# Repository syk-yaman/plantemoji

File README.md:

# Plantemoji: a smart IoT plant caring system

A smart plant caring and irrigation device with a web infrastructure to monitor and control plants environment and explain their living state in emojis. Basically, your plant will have AI and will be able to talk with you using emojis!

Plant container			          							 |Water bucket	 
:-----------------------------------------------------------:|:-------------------------------------------------------------------------:|
|   

## Repository Content Summary

1. **3D Enclosures**

   This section includes the 3D printed parts, namely Fusion360 project files and STLs.

   - [Plant pot](</3D Enclosures/Plant pot/>)
   - [Water bucket](</3D Enclosures/Water bucket/>)

2. **Code**

   Includes micro-controllers' code, Artificial Intelligence code and various assets used during development.

   - [AI](/Code/AI)

     [LSTM.py](/Code/AI/LSTM.py) is the main Python script where the LSTM neural network is developed and trained. This folder also contains the old [Colab experiments](/Code/AI/Colab expirements/), which are obsolete and currently kept for archiving purposes. Finally, the [Results](/Code/AI/Results/) folder, which contains experiments' charts for both the LSTM.py and the obsolete Colab experiments.

   - [Assets](/Code/Assets)

     Contains `.bmp` files to be visualised on the screen, in addition to their original Photoshop files `.psd`

   - [ATMega8A](/Code/ATMega8A)

     C program for the AVR micro-controller.

   - [ESP32](/Code/ESP32)

     C++ code for the main micro-controller, which will replace Huzzah.

   - [Huzzah](/Code/Huzzah)

     C++ code for the old micro-controller. It will replaced by ESP32.

3. **Datasets**

   Includes 1 month dataset (the [full dataset](/Datasets/Full)) and other partial datasets used to train the AI model.

   This section also contains some [data analysis](/Datasets/Analysis/Analysis.md).

4. **Docs**

   This folder holds different kinds of documentation and images produced during project life time.

5. **PCB**

   The electronic side of the project. This section contains Eagle files and CAM outputs sent to PCB manufacturers.

6. **Server**

   Docker Composer file for InfluxDB and Grafana. Basically, all data acquisition is being managed by this Docker image.

## Project Overview

This conceptual diagram explains how the system is composed, down from reading sensors and understanding their values, and later sending them up to the cloud for further analysis and visualisation.

The objectives of this plant monitor are:
 - Interpret sensor data for the end user in a human-friendly way.
 - Take into consideration plant living requirements during the monitoring process.
 - Make comparisons between different soil moisture sensors and the same sensor in different conditions.

## Building

### Used components and tools

Hardware:
 - [Arduino UNO](https://store.arduino.cc/products/arduino-uno-rev3)
 - [Adafruit Feather HUZZAH ESP8266](https://learn.adafruit.com/adafruit-feather-huzzah-esp8266/)
 - Huzzah-DHT22 CASA shield ([From here](https://github.com/ucl-casa-ce/casa0014/blob/main/plantMonitor/README.md#multiple-physical-prototypes))
 - [DH22](https://www.adafruit.com/product/385): Humidity and temperature sensor 
 - [HW-390](https://thepihut.com/products/capacitive-soil-moisture-sensor?variant=32137736421438): Capacitive Soil Moisture Sensor 
 - [Waveshare 1.47" LCD Dislay](https://thepihut.com/products/1-47-rounded-spi-lcd-display-module-172x320?variant=42062646509763)

Software:
 - [InfluxDB](https://www.influxdata.com/)
 - [Telegraf](https://www.influxdata.com/time-series-platform/telegraf/)
 - [Grafana](https://grafana.com/)
 - [Docker Compose](https://docs.docker.com/compose/)

All the software applications are packed into one [Docker image](/Server/docker-compose.yml) that you can use easily.

Tools:
 - [Image2Lcd](https://www.waveshare.com/wiki/File:Image2Lcd.7z): converts BMP images to byte arrays stored in MCUs to be displayed on the LCD screen (please follow [these settings](/Docs/Image2LCD%20app%20settings.jpg)).

### Hardware schematic

### Highlights
 - Sensors are connected to Arduino now due to the availability of many ADC ports compared to HUZZAH.
 - The LCD screen driver was ported from Arduino to work on HUZZAH, the latter has more memory and capability to drive screens compared to Arduino.
 - New MQTT topics added: `moistureCapacitive` for the capacitive sensor and `mood` which is derived from sensor data according to plant profile.
 - [Plant profile](/Code/Huzzah/PlantProfile.h): a file containing the suitable living environment parameters for the desired plant. The mood of the plant (happy - sad) is determined based on this profile.

## Results
Grafana dashboard            |  InfluxDB dashboard		 |  MQTT feed
:---------------------------:|:-------------------------:|:-------------------------:
|   |   

See [here](/Docs/DAQ/DAQ.md) for more detailed comparisons between sensor types.

## Future work
- Add more plants profiles.
- Let plant profile can be controlled using HTTP.
- Add mobile notifications.
- Do more comparisons with other sensor conditions.
- Add more emojis to express plant mood further.

## Resources and references
- [Capacitive sensors principles](https://makersportal.com/blog/2020/5/26/capacitive-soil-moisture-calibration-with-arduino)
- [Serial communication](https://circuitdigest.com/microcontroller-projects/arduino-spi-communication-tutorial)
- [InfluxDB course](https://university.influxdata.com/courses/influxdb-essentials-tutorial/)

## Lessons learned
 - Understanding the data from a simple sensor in the real world is not easy due to the effect of environment parameters and setup conditions.
 - Remember: Always print a 3D case and try to be gentle with screens!
 - Visualising the data can make us understand the surrounding environment in a better way.
 - If a serial connection is needed between two devices with different power sources, their GND should be connected together. And of course, they also must have the same baud rate.

## License

###### The software side is licensed under MIT License

```
MIT License

Permission is hereby granted, free of charge, to any person obtaining a copy
of this software and associated documentation files (the "Software"), to deal
in the Software without restriction, including without limitation the rights
to use, copy, modify, merge, publish, distribute, sublicense, and/or sell
copies of the Software, and to permit persons to whom the Software is
furnished to do so, subject to the following conditions:

The above copyright notice and this permission notice shall be included in all
copies or substantial portions of the Software.

THE SOFTWARE IS PROVIDED "AS IS", WITHOUT WARRANTY OF ANY KIND, EXPRESS OR
IMPLIED, INCLUDING BUT NOT LIMITED TO THE WARRANTIES OF MERCHANTABILITY,
FITNESS FOR A PARTICULAR PURPOSE AND NONINFRINGEMENT. IN NO EVENT SHALL THE
AUTHORS OR COPYRIGHT HOLDERS BE LIABLE FOR ANY CLAIM, DAMAGES OR OTHER
LIABILITY, WHETHER IN AN ACTION OF CONTRACT, TORT OR OTHERWISE, ARISING FROM,
OUT OF OR IN CONNECTION WITH THE SOFTWARE OR THE USE OR OTHER DEALINGS IN THE
SOFTWARE.
```

###### The hardware side is licensed under CERN License

```
This documentation describes Open Hardware and is licensed under the CERN OHL v. 1.2.

You may redistribute and modify this documentation under the terms of the CERN OHL v.1.2. (http://ohwr.org/cernohl). This documentation is distributed WITHOUT ANY EXPRESS OR IMPLIED WARRANTY, INCLUDING OF MERCHANTABILITY, SATISFACTORY QUALITY AND FITNESS FOR A PARTICULAR PURPOSE. Please see the CERN OHL v.1.2 for applicable conditions
```

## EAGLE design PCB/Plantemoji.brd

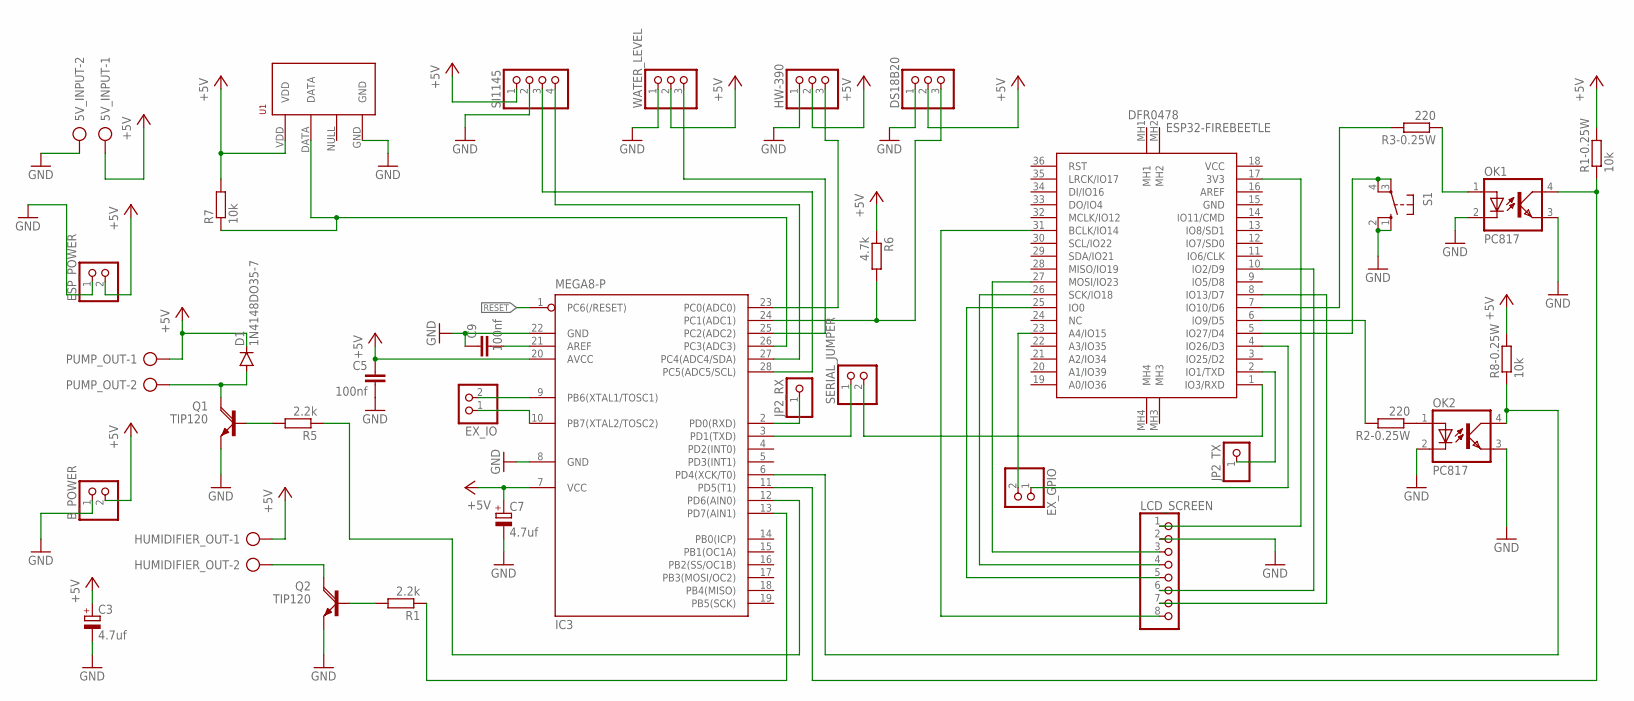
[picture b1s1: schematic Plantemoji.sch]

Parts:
5V_INPUT: AK500/2
B_POWER: PINHD-1X2; 1X02
C3, C7: 4.7uf; E2,5-5
C5, C9: 100nf; C025-025X050
D1: 1N4148DO35-7; DO35-7
DS18B20: PINHD-1X3; 1X03
ESP32-FIREBEETLE: DFR0478; FIREBEETLE_ESP32
ESP_POWER: PINHD-1X2; 1X02
EX_GPIO: PINHD-1X2; 1X02
EX_IO: PINHD-1X2; 1X02
HUMIDIFIER_OUT: AK500/2
HW-390: PINHD-1X3; 1X03
IC3: MEGA8-P; DIL28-3
JP2_RX, JP2_TX: PINHD-1X1; 1X01
LCD_SCREEN: PINHD-1X8; 1X08
OK1, OK2: PC817; DIL04
PUMP_OUT: AK500/2
Q1, Q2: TIP120; TO220AH
R1, R5: 2.2k; 0207/10
R1-0.25W, R7, R8-0.25W: 10k; 0207/10
R2-0.25W, R3-0.25W: 220; 0207/10
R6: 4.7k; 0207/10
S1: 10-XX; B3F-10XX
SERIAL_JUMPER: PINHD-1X2; 1X02
SI1145: PINHD-1X4; 1X04
U1: RHT03_DHT-22_AM2302; RHT03_DHT-22
WATER_LEVEL: PINHD-1X3; 1X03

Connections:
+5V: 5V_INPUT.1, B_POWER.2, C3.+, C5.1, C7.+, D1.C, DS18B20.2, ESP_POWER.2, HUMIDIFIER_OUT.1, HW-390.2, IC3.7 (VCC), IC3.20 (AVCC), PUMP_OUT.1, R1-0.25W.2, R6.1, R7.2, R8-0.25W.2, SI1145.1, U1.VDD, WATER_LEVEL.2
GND: 5V_INPUT.2, B_POWER.1, C3.-, C5.2, C7.-, C9.2, DS18B20.1, ESP_POWER.1, HW-390.1, IC3.8 (GND), IC3.22 (GND), LCD_SCREEN.2, OK1.2 (C), OK1.3 (EMIT), OK2.2 (C), OK2.3 (EMIT), Q1.E, Q2.E, S1.1 (S), S1.2 (S1), SI1145.2, U1.GND, WATER_LEVEL.1
unnamed: ESP32-FIREBEETLE.5 (IO27/D4), S1.3, S1.4 (P1)
unnamed: IC3.3 (PD1(TXD)), SERIAL_JUMPER.1
unnamed: ESP32-FIREBEETLE.1 (IO3/RXD), SERIAL_JUMPER.2
unnamed: ESP32-FIREBEETLE.17 (3V3), LCD_SCREEN.1
unnamed: ESP32-FIREBEETLE.27 (MOSI/IO23), LCD_SCREEN.3
unnamed: ESP32-FIREBEETLE.26 (SCK/IO18), LCD_SCREEN.4
unnamed: ESP32-FIREBEETLE.8 (IO13/D7), LCD_SCREEN.7
unnamed: ESP32-FIREBEETLE.25 (IO0), LCD_SCREEN.5
unnamed: ESP32-FIREBEETLE.10 (IO2/D9), LCD_SCREEN.6
unnamed: IC3.6 (PD4(XCK/T0)), OK2.4 (COL), R8-0.25W.1
unnamed: OK2.1 (A), R2-0.25W.1
unnamed: ESP32-FIREBEETLE.6 (IO9/D5), R2-0.25W.2
unnamed: C9.1, IC3.21 (AREF)
unnamed: OK1.1 (A), R3-0.25W.1
unnamed: ESP32-FIREBEETLE.7 (IO10/D6), R3-0.25W.2
unnamed: IC3.2 (PD0(RXD)), JP2_RX.1
unnamed: ESP32-FIREBEETLE.2 (IO1/TXD), JP2_TX.1
unnamed: D1.A, PUMP_OUT.2, Q1.C
unnamed: Q1.B, R5.2
unnamed: IC3.12 (PD6(AIN0)), R5.1
unnamed: HUMIDIFIER_OUT.2, Q2.C
unnamed: Q2.B, R1.2
unnamed: IC3.13 (PD7(AIN1)), R1.1
unnamed: HW-390.3, IC3.23 (PC0(ADC0))
unnamed: IC3.25 (PC2(ADC2)), WATER_LEVEL.3
unnamed: DS18B20.3, IC3.24 (PC1(ADC1)), R6.2
unnamed: IC3.26 (PC3(ADC3)), R7.1, U1.DATA
unnamed: IC3.28 (PC5(ADC5/SCL)), SI1145.3
unnamed: IC3.27 (PC4(ADC4/SDA)), SI1145.4
unnamed: ESP32-FIREBEETLE.31 (BCLK/IO14), LCD_SCREEN.8
unnamed: ESP32-FIREBEETLE.23 (A4/IO15), EX_GPIO.2
unnamed: EX_IO.2, IC3.9 (PB6(XTAL1/TOSC1))
unnamed: EX_IO.1, IC3.10 (PB7(XTAL2/TOSC2))
unnamed: ESP32-FIREBEETLE.4 (IO26/D3), EX_GPIO.1
unnamed: IC3.11 (PD5(T1)), OK1.4 (COL), R1-0.25W.1
RESET: IC3.1 (PC6(/RESET))

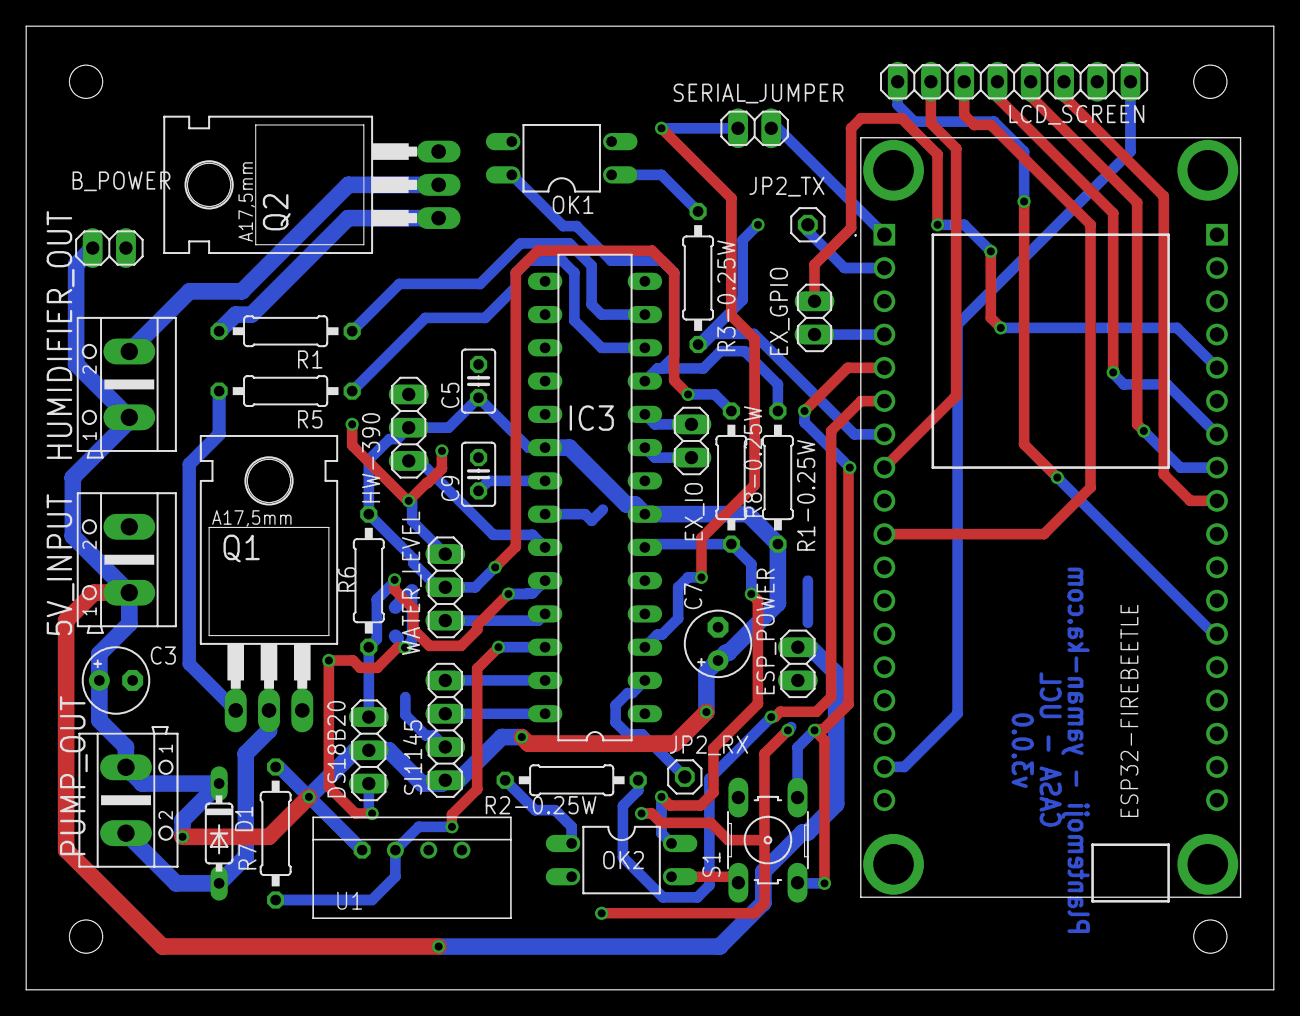
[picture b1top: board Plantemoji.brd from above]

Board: 2 copper layers, 95.3 x 73.6 mm, 36 parts (0 on the bottom side), 37 nets.

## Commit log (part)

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2022-10-26 Now sending updates via MQTT is working
2022-10-28 Adding LCD library
2022-10-28 First image displayed!
2022-10-28 Trying to display a sad face now
2022-10-28 No enough memory space to include both happy & sad face... I have to draw the happy face programmatically :(
2022-10-28 Remove the not used Chinese font
2022-10-29 Trying to draw a face, added a new yellow colour
2022-10-29 Trying to port the LCD driver to Huzzah, after a lot of attemps, it works now! But got a problem of maximum execution time which I'm try to solve for now
2022-10-29 Solved: by adding a yeild function inside LCD driver; turned out Huzzah doesn't allow more than 1.5 seconds for any loop to be executed
2022-10-29 Adding a new happy face and display it on screen
2022-10-29 For future documentation, added a screenshot for the Image2LCD application
2022-10-29 Change the sad image to a bigger size
2022-10-29 Read soil moisture level and display it on screen
2022-10-29 Sort up all code into new folders
2022-10-29 Added emoji PSD assets
2022-10-31 Add a string splitting function
2022-10-31 Move screen output to setup function, just for now
2022-10-31 First real Serial connection from Arduino to Huzzah, now sending fake sensor data in real time
2022-10-31 Remove LCD code from Arduino because I decided to connect it to Huzzah instead
2022-10-31 Sorting up LCD driver code
2022-10-31 Read LDR value from Arduino and send it to Huzzah
2022-10-31 Read humidity & temperature values from Arduino and send them to Huzzah
2022-10-31 Trying to re-add MQTT code to publish the new data
2022-10-31 Trying to connect to WPA2 Enteprise (eduroam)... seems it won't work
2022-10-31 Revert all WPA2 changes
2022-10-31 For comparison reasons; adding the nails again to compair values with the capacitive sensor
2022-10-31 Adding the new nails moisture to MQTT publish
2022-10-31 Remove LDR sensor values for now
2022-11-01 Added a working dockerised version of CE lab setup, now is hosted on yaman-ka.com
2022-11-01 Fixing folder name
2022-11-01 Implement mood logic and send to MQTT
2022-11-01 Correct my moisture MQTT topics (nails & capacitive)
2022-11-01 Sort up Arduino code & some refactoring
2022-11-01 Sort up Huzzah code & some refactoring
2022-11-02 Add my telegraf configs
2022-11-02 Add my Grafana dashboard sample
2022-11-02 Move plant parameters to a seperate plant profile file
2022-11-02 Add docs for plant profile
2022-11-02 Add a system mind map to README.md
2022-11-02 README correction
2022-11-02 Added a main photo
2022-11-02 Try to make sure if Github can detect empty lines in md
2022-11-02 Add README outline and some lessons learned
2022-11-02 Add a schematic diagram
2022-11-02 Begin adding links
2022-11-02 Finish adding used components
2022-11-02 Correct links
2022-11-02 Also correct links
2022-11-02 Added Image2Lcd reference
2022-11-02 Also complete working on README
2022-11-02 Also continue working on readme
2022-11-02 Readme update
2022-11-02 Add some results
2022-11-02 Edit results table
2022-11-02 Unify results table
2022-11-02 Add DAQs
2022-11-02 Link DAQ in readme
2022-11-02 Correct data lists in docs
2022-11-02 Add future work and references
2022-11-02 Add InfluxDB to resources list
2022-11-02 Add licenses
2022-11-02 Update TODO
2022-11-16 Remove Todo and corrected a typo
2022-12-01 Connecting Soil Temperature sensor using Arduino (DS18B20)
2022-12-01 Add a new Atmel Studio project for Atmega8A containing a demo serial connection
2022-12-02 Success in getting soil temperature from the DS18B20 sensor and send it via serial
2022-12-05 Change DS18B20 port
2022-12-05 Add used Eagle libraries
2022-12-05 Create new PCB for plantemoji and finish the first draft of the schematic
2022-12-05 Putting all the components on the board without routing for now
2022-12-06 Finish wiring the PCB
2022-12-06 Final touches before gerber files export
2022-12-06 PCB is sent to PCBWay! Gerber files were generated using this tutorial (https://www.pcbway.com/helpcenter/technical_support/Generate_Gerber_files_in_Eagle.html)
2022-12-09 Added BOM for the PCB
2022-12-10 Added the full water level sensor & pump holders
2022-12-10 Added an Arduino serial echo code (used while connected to ATmega 8A)
2022-12-10 Renamed a g-code file for consistency
2022-12-10 Added Fusion360 project file & re-order 3d design files
2022-12-10 Added a schematic picture for the PCB
2022-12-12 Finished all the 3D enclosures!
2022-12-12 Add an exported version of Fusion360 project
2022-12-14 Change system mind map (overview)
2023-01-20 Remove G-code files as they can be produced from the STL objects
2023-01-20 Re-order code files
2023-01-20 Remove redundant Arduino code
2023-01-20 Remove the old schematic
2023-01-20 Add ATMega8A flashing settings to docs
2023-01-20 Replace schematic diagram
2023-01-20 Add the new photos in Readme.md
2023-01-20 Fix images in Readme.md
2023-01-20 Complete fixing images
2023-01-20 Also fixing images
2023-01-20 Refactor images in Readme.md
2023-02-15 Add the DHT22 library and read values from the sensor
2023-02-15 Fixed a bug: sprintf() wasn't able to format double numbers, this was fixed by enabling the built-in functionality from compiler settings (taken from: https://startingelectronics.org/articles/atmel-A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
2023-02-16 Add the SI1145 codebase - not finished yet
2023-02-16 Failed to compile, codebase now is too big - trying to reduce size
2023-02-19 Continue attempts to make the SI1145 sensor working, the problem is mainly in the I2C connection
2023-02-19 Trying to re-implement I2C connection from scratch
2023-02-20 After several days of debugging, I solved the I2C communication bug with the SI1145. Turned out the AVR TWI interface only includes basic byte exchange operations, without any software implementation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
2023-02-20 Files + code refactoring and adding some documentation
2023-02-20 Fixed a bug in the SI1145_WE library, the address is set after initialisation whether it should be before initialisation!
2023-02-20 Remove redundant files and update .gitignore
2023-02-20 Also redundant files
2023-02-20 Re-add all the sensors and add the final one (HW-390) - soil humidity sensor
2023-02-20 Fix a conflict in serial output, caused somehow internally in the MCU
2023-02-20 Refactoring in main.c
2023-02-21 Finalise the Atmega8A code, now all sensor data are being sent to Huzzah via serial
2023-02-21 Code documentation refactoring
2023-02-21 Add the generated binary for the ATmega8A
2023-02-21 Remove redundant comments
2023-02-21 Re-order and rename sensor readings
2023-02-21 Finish implementing MQTT sensor values publishing on Huzzah
2023-02-21 The new binary for the ATMega8A
2023-02-21 Fix a bug in MQTT transmission; a missing digit was at the end of every sensor value
2023-02-23 Re-scale sensor values and describe all used units in the documentation section
2023-02-23 Correct the soil humidity scale, now it's percentage
2023-02-27 Fix variable overflow bug
2023-02-27 Fix the soil humidity percentage: it was based on the ADC reading and was measuring the anti-humidity actually. Now it's the same unit as the air humidity
2023-03-01 Port the Waveshare LCD driver to ESP32
2023-03-01 Move the new ported ESP32 codebase to a new folder
2023-03-05 Major update to the PCB: now it's based on ESP32 (FireBeetle) instead of the old ESP8266 (Feather Huzzah)
2023-03-05 The new PCB is sent to PCBWay (using this procedure: https://www.pcbway.com/helpcenter/technical_support/Notes_for_Gerber_files_Generated_from_Eagle_9_20.html)
2023-03-05 Add the library used for ESP32 footprint in Eagle (taken from: componentsearchengine.com)
2023-03-09 Trying a demo to auto-control the pump and humidifier
2023-03-09 Fixed a bug: the pump controlling port caused a conflict with the serial output
2023-03-13 Add more documentation for controlling the pump and the humidifier
2023-03-13 Added the pump & humidifier control feature (to be controlled by Huzzah) in addition to reporting these states over serial
2023-03-13 Add a missing documentation
2023-03-13 Add the new values (pump and humidifier states)
2023-03-13 Subscribe to pump and humidifier control topic on MQTT
2023-03-13 Implemented pump and humidifier manual control via MQTT
2023-03-14 Code refactor: using general pin numbers
2023-03-14 Trying to make TinyML demo on ESP32, I used @djdunc 's code from https://github.com/ucl-casa-ce/casa0018/blob/main/Week4/arduino/hello_casa
2023-03-14 Made some adaptations to the TinyML code in order to work on ESP32
2023-03-14 Submit an old experiment, for archiving purposes
2023-03-14 A fix in Readme.md indentation
2023-03-15 Create a Colab document and create a live connection to InfluxDB
2023-03-15 Added time index to the exported file in Colab
2023-03-16 Add an experiment for another DHT22 in the CE lab
2023-03-19 Add the exported air humidity dataset
2023-03-19 Add the exported air temperature dataset
2023-03-19 Add the exported plant infrared dataset
2023-03-19 Add the exported plant light dataset
2023-03-19 Add the exported soil humidity dataset
2023-03-19 Add the exported soil temperature dataset
2023-03-19 Add the exported plant UV dataset
2023-03-19 Update .gitignore to ignore redundant Eagle files
2023-03-20 USE LTSM single variable from CE AI module (https://github.com/djdunc/casa0018/tree/main/Week7)
2023-03-20 Rename Colab file
2023-03-20 Added some LSTM failed experiments :(
2023-03-20 Add some analysis of temperature & humidity readings in CE lab so far
2023-03-20 Add my discussion with Will about the last humidity and temperature results
2023-03-20 Fix data analysis images
2023-03-20 Re-re-correct analysis images
2023-03-20 Re-re-re-fix analysis images :/
2023-03-21 Added a new version of LSTM taken from: https://github.com/google-coral/tutorials/blob/master/train_lstm_timeseries_ptq_tf2.ipynb
2023-03-21 Conversion to TFLite has failed, after a lot of experimenting, this solution worked: https://github.com/tensorflow/tensorflow/issues/50942
2023-03-21 Archive the error that was appearing while converting the model to TFLite
2023-03-21 Fix LSTM python file
2023-03-21 Moved to use local Python environment since Colab has limited my access :/
2023-03-21 Completing merging all sensor readings in the Python script, in preparation to find correlation between them - still facing a problem here
2023-03-21 Fixed an issue with data correlation calculation, turned out Python was importing my sensor values as objects not floats
2023-03-21 Added a merged dataset from 5-3-2023 to 8-3-2023
2023-03-21 Add some results of data correlation and plots
2023-03-21 Add full and partial correlation results
2023-03-21 Complete model training and do some prediction
2023-03-21 'val_loss' was not available due to the small size of dataset, I had to increase the period of InfluxDB query to cover almost a month. As a result, I have changed the past & future variables (related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
2023-03-21 Add more results
2023-03-22 Add new results for soil humidity and re-arrange the old results files
2023-03-22 Add the unified dataset from 22-2-2023 to 20-3-2023
2023-03-22 Add new screen images and docs
2023-03-22 Fix the old happy emoji
2023-03-22 Display the new images to show the watering status
2023-03-22 Add an attempt to remove outliers
2023-03-23 The manual standard deviation scaling method provided by Google did not work. I had to use the MinMaxScaler from sklearn instead
2023-03-23 Add the conversion steps to the main Python file, with the quantization process, and finally the final tests to make sure the quantized model is generating the right values
2023-03-23 Add some documentation inside the main Python file
2023-03-23 Folders refactoring
2023-03-23 Remove wrong AI results, turned out these were air humidity values
2023-03-23 Add the generated TFLite air humidity prediction model
2023-03-23 Add air humidity AI results
2023-03-24 Change main device photo in Readme.md
2023-03-24 Add repo summary to Readme.md
2023-03-24 Fixed links in Readnme.md
2023-04-24 Show a QR code on the LCD screen to connect with the mobile app
2023-04-30 Fix the scaling issue in plotting results & use only soil moisture for now
